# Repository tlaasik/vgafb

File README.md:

# VgaFB

Minimalistic VGA framebuffer hardware and software for microcontrollers (right now only tested on Arduino Uno and Nano).

## Features
* simple hardware (just 3x2:1 mux and 64KB SPI memory chip), but just enough to have low CPU utilization
* has integraion with high level u8g2 and u8x8 API. These provide monochrome font and graphics rendering
* supports 2 colors: black and a color selected by RGB jumper
* up to 640x480 resolution (64KB address space, 1bit per pixel)
* fast screen clear and fast vertical scrolling
* (optional) generates pixel clock by multiplying MCU clock by 2x 2.5x 3x 4x or 5x
* (optional) or generates pixel clock with own oscillator 20MHz 25MHz 30Mhz 40MHz 50MHz. MCU should use it

## Usage
1. Decide how to generate pixel clock, this may limit what resolutions are available. For example, Arduino may run at 16MHz and generate 8MHz that is fed into CLKIN. Then using 2.5x multiplier 20MHz pixel clock is generated suitable for 400x300@60Hz and 256x256@60Hz modes
2. Wire this schematic together with your Arduino board or chip
3. Download [arduino_lib/](arduino_lib/) and place the contents where your arduino libraries are (usually c:\Users\<username>3\Documents\Arduino\libraries\) or directly in your project folder
4. See [arduino_lib/examples/TextOnScreen_8x2g.ino](arduino_lib/examples/TextOnScreen_8x2g.ino)

List of modes supported (format tells screen width and height, refresh rate and required pixel clock)
* vgamode_400x300_60Hz_20MHz
* vgamode_256x256_60Hz_20MHz
* vgamode_640x480_75Hz_32MHz
* vgamode_320x240_75Hz_16MHz
* vgamode_640x400_85Hz_32MHz
* vgamode_320x200_85Hz_16MHz
* vgamode_640x480_60Hz_25MHz
* vgamode_320x240_60Hz_12_6MHz
* vgamode_160x120_60Hz_6_3MHz

Wiring to Arduino Nano
```
vgafb  ardu_nano
-------------------------------------
SCL    -       monitor I2C DDC clock, no need to connect
SDA    -       monitor I2C DDC data, no need to connect
+5V    +3..5V
GND    ground
SCK    D13     SPI clock in
MISO   D12     SPI data out
MOSI   D11     SPI data in
VSYNC  D10     vertical sync in
/SEL   D4      SPI memory chip select in
CLKIN  D3      clock in, it's multiplied to get pixel clock (right now VgaFB_Begin configures it to 8MHz)
A      D9      mode in if normal vsync, leave hi-z or drive high if inverted vsync
B      D8      mode in if inverted vsync, leave hi-z or drive high if normal vsync
HS     D5      horizontal sync in
PX     -       pixel clock out (without clock mult. chip it's pixel clock in)

/SEL, A and B pins can be assigned elsewhere on Arduino Nano. Other pins are fixed due
to hardware resources like PWM and SPI tied to specific pins.
```

## Example code
```C
#include <U8x8lib.h>
#include <SPI.h>
#include <VgaFB_u8x8.h>

U8G2_VGAFB_400X300_60Hz_20MHz_GENERIC_1_VGAFBBUS u8g2(U8G2_R0, /*mul/div=*/5, 4, /* cs=*/ 4, /* a=*/ 9);

// Generate 8MHz that will be multiplied by 2.5 (set by jumpers) to get 20MHz pixel clock.
// Since Arduino itself runs at 16MHz we told in u8g2 constructor that the multiplier is 1.25
void setupClockGen() {
	OCR2A = 0;
	TCCR2A = _BV(WGM21) | _BV(COM2B0); // toggle B on compare (pin 5, Arduino port: D3)
	TCCR2B = 1; // prescale 1
	pinMode(3, OUTPUT);
}
void setup() {
	setupClockGen();
	u8g2.begin();
}
void loop() {
	u8g2.firstPage();
	do {
		u8g2.setFont(u8g2_font_ncenB14_tr);
		u8g2.drawStr(0, 20, "VGA framebuffer for Arduino Nano");
		u8g2.drawStr(130, 260, "Running at 400x300 60Hz");
		u8g2.setFont(u8g2_font_ncenB08_tr);
		u8g2.drawStr(130, 280, "Using u8g2 for rendering text");
		u8g2.drawStr(0, 40, "https://github.com/tlaasik/vgafb");
		u8g2.drawFilledEllipse(100, 100, 90, 30);
	} while (u8g2.nextPage());
	
	_delay_ms(4000);
	VgaFB_Scroll(u8g2.getVgaFB(), 300);
	_delay_ms(800);
}
```

## Low level C API (not safe, buf fast)
```C
void VgaFB_ConfigBoard(vgafb_t * vgafb, uint8_t mul, uint8_t div, uint8_t cs_pin, uint8_t ab_pin);
bool VgaFB_Begin(vgafb_t * vgafb, vgamode_t mode);
void VgaFB_End(vgafb_t * vgafb);
void VgaFB_DisplayEnabled(vgafb_t * vgafb, bool enabled);
void VgaFB_Clear(vgafb_t * vgafb);
void VgaFB_Scroll(vgafb_t * vgafb, int16_t deltaScanline);
void VgaFB_Write(vgafb_t * vgafb, uint_vgafb_t dst, uint8_t * src, uint_vgafb_t cnt);
void VgaFB_Read(vgafb_t * vgafb, uint_vgafb_t src, uint8_t * dst, uint_vgafb_t cnt);
// uint_vgafb_t is usually uint16_t (VGAFB_VRAM_ADDR_LENGTH==2)
```

## Pictures of it working

(used an old monitor, because it supported more refresh rates on low resolution than my more modern LCD)

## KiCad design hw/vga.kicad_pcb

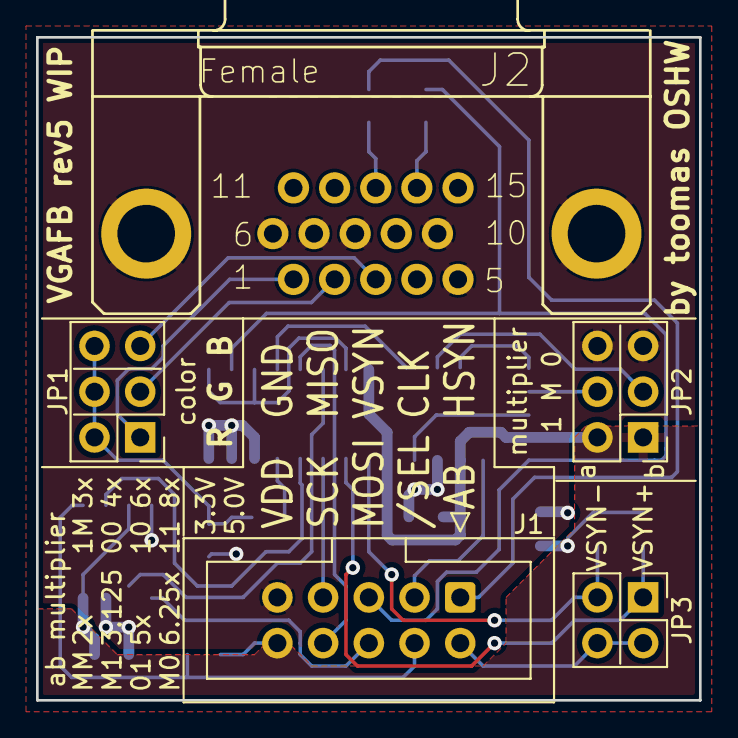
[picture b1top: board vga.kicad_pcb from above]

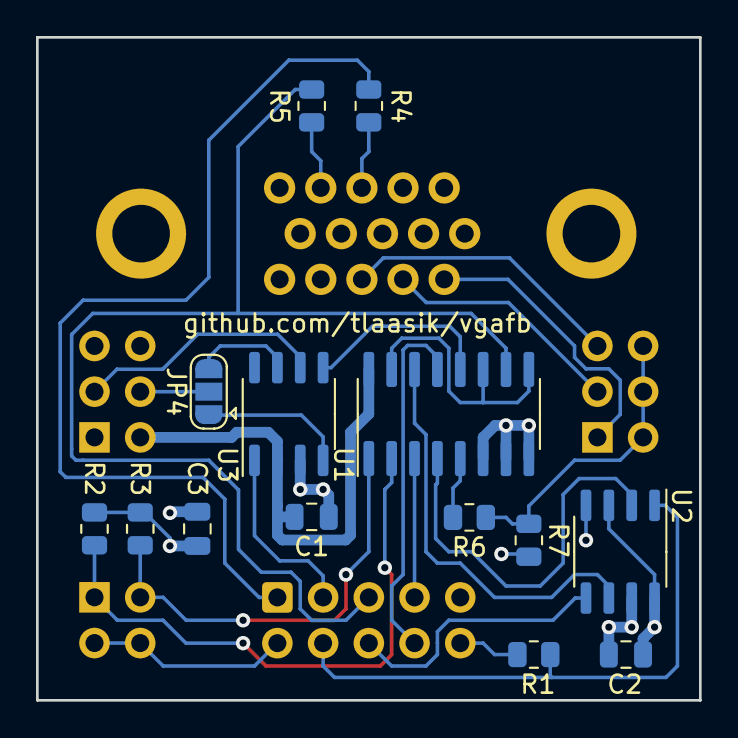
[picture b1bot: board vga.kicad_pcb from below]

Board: 2 copper layers, 36.8 x 36.8 mm, 19 parts (14 on the bottom side), 27 nets.

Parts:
C1, C2: 10n; C_0805_2012Metric
C3: 100n; C_0805_2012Metric
J1: Conn_02x05_Odd_Even; IDC-Header_2x05_P2.54mm_Vertical
J2: DB15_Female_HighDensity_MountingHoles; con-subd-HDF15H
JP1: color; PinHeader_2x03_P2.54mm_Vertical
JP2: multiplier; PinHeader_2x03_P2.54mm_Vertical
JP3: Conn_02x02_Odd_Even; PinHeader_2x02_P2.54mm_Vertical
JP4: SolderJumper_3_Bridged12; SolderJumper-3_P1.3mm_Open_RoundedPad1.0x1.5mm
R1, R2, R3: 10k; R_0805_2012Metric
R4, R5: 22; R_0805_2012Metric
R6: 220; R_0805_2012Metric
R7: 100; R_0805_2012Metric
U1: 74HC4053; SOIC-16_3.9x9.9mm_P1.27mm
U2: 23LCV512; SO-8_3.9x4.9mm_P1.27mm
U3: ICS501; SO-8_3.9x4.9mm_P1.27mm

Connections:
/AB: J1.2, JP3.2, JP3.4
/CLKIN: J1.3, U3.1 (X1_ICLK)
/HSYNC: J1.1, R4.2
/MISO: J1.7, U1.3 (IN1)
/MOSI: J1.6, U2.5 (SI)
/PIXEL: R6.2, U1.5 (IN0)
/PXCLK: U1.12 (IN0), U3.5 (CLK)
/PX_B: J2.3, JP1.5
/PX_G: J2.2, JP1.3
/PX_R: J2.1, JP1.1
/S0_a: JP2.3, U3.6 (S0)
/S1_b: JP2.4, JP4.2 (C)
/SCK: J1.8, U1.13 (IN1)
/VSYNC: J1.5, R5.2, U1.10 (S)
//SEL: J1.4, R1.1, U2.1 (~CS)
GND: C1.2, C2.2, C3.2, J1.9, J2.0, J2.5, J2.6, J2.7, J2.8, J2.10, JP2.5, JP2.6, R7.2, U1.6 (INH), U1.7 (VEE), U1.8 (GND), U2.4 (GND), U2.7 (~HOLD), U3.3 (GND)
unnamed: J2.13, R4.1
unnamed: J2.14, R5.1
unnamed: JP1.2, JP1.4, JP1.6, R6.1, R7.1
unnamed: JP3.1, R2.2, U1.2 (IN0)
unnamed: JP3.3, R3.2, U1.1 (IN1)
unnamed: JP4.1 (A), U3.4 (S1)
unnamed: JP4.3 (B), U3.7 (OE)
unnamed: U1.4 (OUT), U2.2 (SO)
unnamed: U1.9 (S), U1.11 (S), U1.15 (OUT)
unnamed: U1.14 (OUT), U2.6 (SCK)
VDD: C1.1, C2.1, C3.1, J1.10, JP2.1, JP2.2, R1.2, R2.1, R3.1, U1.16 (VDD), U2.3 (~WP), U2.8 (VDD), U3.2 (VDD)

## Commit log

2017-06-06 Added rev3 hardware schematic and board
2017-06-06 First Arduino library code commit
2017-06-07 Added pictures for linking in wiki
2017-06-07 Added picture
2017-06-07 Changed resolution in an example
2017-06-12 Added code to support >64kB memories
2017-06-12 Moved clock gen code out from vgafb core. Added VgaFB_ClearLine
2017-06-13 Removed clearLine from core code
2017-06-13 Added 256x256 mode (400x300 variant, but partial screen)
2017-06-13 Fixed pixel height for doublescan modes
2017-06-13 Refactored u8g2 constructors to have less lines of code
2017-06-13 Updated example code
2017-06-13 Removed TimerHelpers.h dependency
2017-06-13 A bit faster vgafb transaction wait routine. Added VGAFB_VRAM_SIZE
2017-06-13 Added VgaFB_DisplayEnabled()
2017-06-15 Cleaner VRAM address length code and a bit better header files
2017-06-15 Vga flags are now in an enum
2017-06-15 Added header file comments
2017-06-15 Added VgaFB class. Added more video modes (untested)
2017-06-15 Chagned Arduino code license to LGPL
2017-06-15 Updated display modes in readme
2017-06-16 Added Adafruit GFX library integration. Changed VgaFB U8G2 constructors
2017-06-16 Changed VgaFB U8X8 constructors
2017-06-16 Moved GetPixel and SetPixel to VgaFB_core
2017-06-16 VgaFB is now constructed the same way as VgaFB_GFX
2017-06-16 Cleaned up includes and method names
2017-06-16 More cleanup
2017-06-16 Added power save mode to VgaFB U8x8 and U8g2
2017-06-16 Moved some of VRAM access into defines
2017-06-17 Updated example
2017-06-17 Clear method now restores state, not just re-enable vgafb
2017-06-17 Added Trim method that's called automatically to speed up vram access
2022-09-08 Upgraded project to Kicad 6
2022-09-26 Changed PLL chip to ICS501 and removed onboard oscillator option. Changed J1 footprint to 14 pin double row pin header. Swapped J1 pins 2 and 3 (hsync and B). J1 pin 1 is now ground (used to be pixel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
2022-09-30 Reduced J1 to 10pins by removing all non-essential pins. Reviewed comments on the schematic. Added solder jumper so that more PLL chips could be used. Changed AB input to use pullups like rev3 did (b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
2022-10-06 Finalized rev4 board. Added post PCB manufacturing TODOs to schematic.
2022-10-07 Updated folder structure
2022-10-07 U8g2 example now checks if U8G2_16BIT is defined
2022-10-07 Changed 256x256_60Hz_20MHz mode to 240x240 so that it would be usable if U8G2_16BIT is not defined
2022-10-07 VgaFB_u8g2 can now call all VgaFB_core methods directly (no need to use VgaFB like before)
2022-10-07 Removed some methods from VgaFB_u8g2 that already have good alternatives
2022-10-11 Cleaned up the schematic and changed some resistor values for better impedance matching
